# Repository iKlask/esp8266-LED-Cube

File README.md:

# esp8266-LED-Cube
This is a Blynk based Arduino LED Cube. The cube is a 3x3x3 matrix of LEDs which are controlled via the internet over the Blynk API with an app or with their RESTful api.

### Arduino Library Requirements:
* [Arduino IDE esp8266 Library](https://arduino-esp8266.readthedocs.io/en/latest/installing.html#boards-manager)
* [Blynk Library](https://www.blynk.cc/getting-started/)
* [WifiManager Library](https://github.com/tzapu/WiFiManager)
* [SimpleTimer Library](https://github.com/schinken/SimpleTimer)

Here is a bill of material with the part numbers I used:

* (x1) ESP-01 esp8266 module
   - Any generic ESP-01 should work
* (x2) 74hc595 Shift Register ICs
   - SN74hc595N
* (x27) 3mm LED (I used Red 1.85v LEDs)
   - WP710A10SRD/E
* (x3) 2n3904 NPN Transistors
   - 2N3904TA
* (x3) 1k Ohms Resistors
   - CF14JT1K00
* (x2) 330 Ohms Resistors
   - CF14JT330R
* (x3) 220 Ohms Resistors
   - CF14JT220R
* (x1) TO-220 3.3v Linear Voltage Regulator
   - LD1117V33C
* (x2) Radial 10uF 50VDC 2mm Electrolytic Capacitors
   - SKR100M1HD11M
* (x1) DC Barrel jack
   - PJ-102AH
* (x1) Barrel Jack Power supply (Must fit the LD1117v33C input requirements)
   - SunFounder DC 9V/650mA Power Supply Plug Adapter
* Break away headers
    - 2 pins for access to Rx/Tx
    - 3 pins + jumper for restarting in programming mode
        - Alternativley use a mini 3 pin single pole, double throw (SPDT) switch

You can copy my project by scanning this QR into the Blynk app. You'll need to supply your new Authtoken in the sketch's ```char auth[]``` field.

The current sketch expects the following on a Blynk App:

* A Blynk Text LCD to display what the current animation is
   - Input: V2
* A Blynk Menu for Changing the animation of the cube.
   - Output: V0
   - Animations are set to the following indices
       1. Random
       2. Slither
       3. Center Spin
       4. Rain
       5. Flip
       6. Windmill
* A Blynk Slider to adjust the speed of the animations.
   - Output: V1
   - This number is applied as a delay between each "draw", so higher numbers mean slower animations
   - I have mine set to decimal values between 50-5000

A project post-mortem can be seen [here.](https://iklask.github.io/blog/wifi-enabled-3d-led-cube/)

Schematic of the PCB here:

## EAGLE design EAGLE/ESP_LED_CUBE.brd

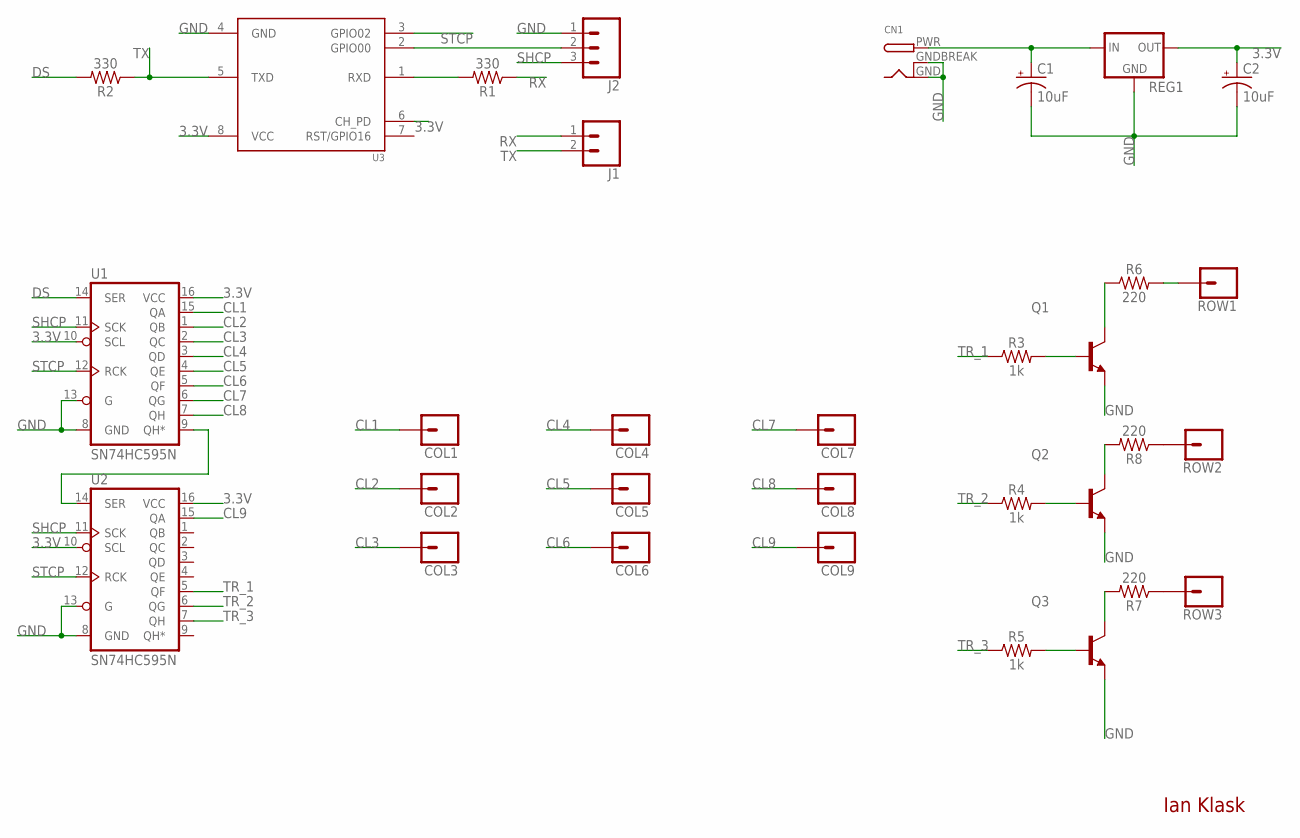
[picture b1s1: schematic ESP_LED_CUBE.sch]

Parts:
C1, C2: 10uF; CPOL-RADIAL-2.5MM-5MM
CN1: DCBARRELPTH; DCJACK_2MM_PTH
COL1, COL2, COL3, COL4, COL5, COL6, COL7, COL8, COL9: CONN_01; 1X01
J1: CONN_02; 1X02
J2: CONN_03; 1X03
Q1, Q2, Q3: 2N3904; TO92
R1, R2: 330; AXIAL-0.3
R3, R4, R5: 1k; AXIAL-0.3
R6, R7, R8: 220; AXIAL-0.3
REG1: V_REG_LD1117VXX; 78XXL
ROW1, ROW2, ROW3: CONN_01; 1X01
U1, U2: SN74HC595N; DIP16
U3: ESP8266-01/ESP-01; XCVR_ESP8266-01/ESP-01

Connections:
3.3V: C2.1 (+), REG1.GND (OUT), U1.10 (SCL), U1.16 (VCC), U2.10 (SCL), U2.16 (VCC), U3.6 (CH_PD), U3.8 (VCC)
CL1: COL1.1, U1.15 (QA)
CL2: COL2.1, U1.1 (QB)
CL3: COL3.1, U1.2 (QC)
CL4: COL4.1, U1.3 (QD)
CL5: COL5.1, U1.4 (QE)
CL6: COL6.1, U1.5 (QF)
CL7: COL7.1, U1.6 (QG)
CL8: COL8.1, U1.7 (QH)
CL9: COL9.1, U2.15 (QA)
DS: R2.P$2 (2), U1.14 (SER)
GND: C1.2 (-), C2.2 (-), CN1.GND, CN1.GNDBREAK, J2.1, Q1.3 (E), Q2.3 (E), Q3.3 (E), REG1.IN (GND), U1.8 (GND), U1.13 (G), U2.8 (GND), U2.13 (G), U3.4 (GND)
unnamed: C1.1 (+), CN1.PWR, REG1.OUT (IN)
unnamed: U1.9 (QH*), U2.14 (SER)
unnamed: R1.P$2 (2), U3.1 (RXD)
unnamed: Q1.1 (C), R6.P$1 (1)
unnamed: R7.P$1 (1), ROW3.1
unnamed: R8.P$1 (1), ROW2.1
unnamed: R6.P$2 (2), ROW1.1
unnamed: Q3.1 (C), R7.P$2 (2)
unnamed: Q2.1 (C), R8.P$2 (2)
unnamed: Q3.2 (B), R5.P$2 (2)
unnamed: Q2.2 (B), R4.P$2 (2)
unnamed: Q1.2 (B), R3.P$2 (2)
unnamed: J2.2, U3.2 (GPIO00)
RX: J1.1, R1.P$1 (1)
SHCP: J2.3, U1.11 (SCK), U2.11 (SCK)
STCP: U1.12 (RCK), U2.12 (RCK), U3.3 (GPIO02)
TR_1: R3.P$1 (1), U2.5 (QF)
TR_2: R4.P$1 (1), U2.6 (QG)
TR_3: R5.P$1 (1), U2.7 (QH)
TX: J1.2, R2.P$1 (1), U3.5 (TXD)

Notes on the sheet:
Ian Klask

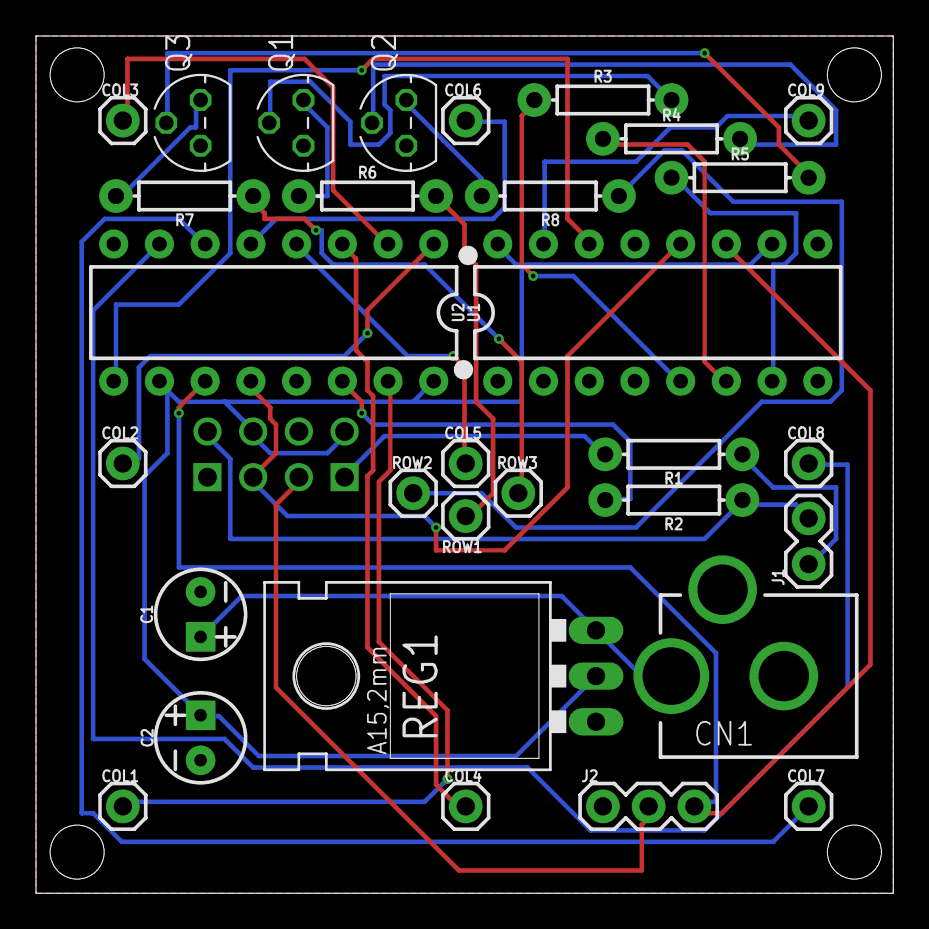
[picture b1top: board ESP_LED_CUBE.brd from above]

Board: 2 copper layers, 47.6 x 47.6 mm, 32 parts (1 on the bottom side), 32 nets.

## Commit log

2019-03-02 ReadMe update

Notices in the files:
parts and their libraries:
SparkFun-Capacitors: Licensing: Creative Commons ShareAlike 4.0 International - https://creativecommons.org/licenses/by-sa/4.0
